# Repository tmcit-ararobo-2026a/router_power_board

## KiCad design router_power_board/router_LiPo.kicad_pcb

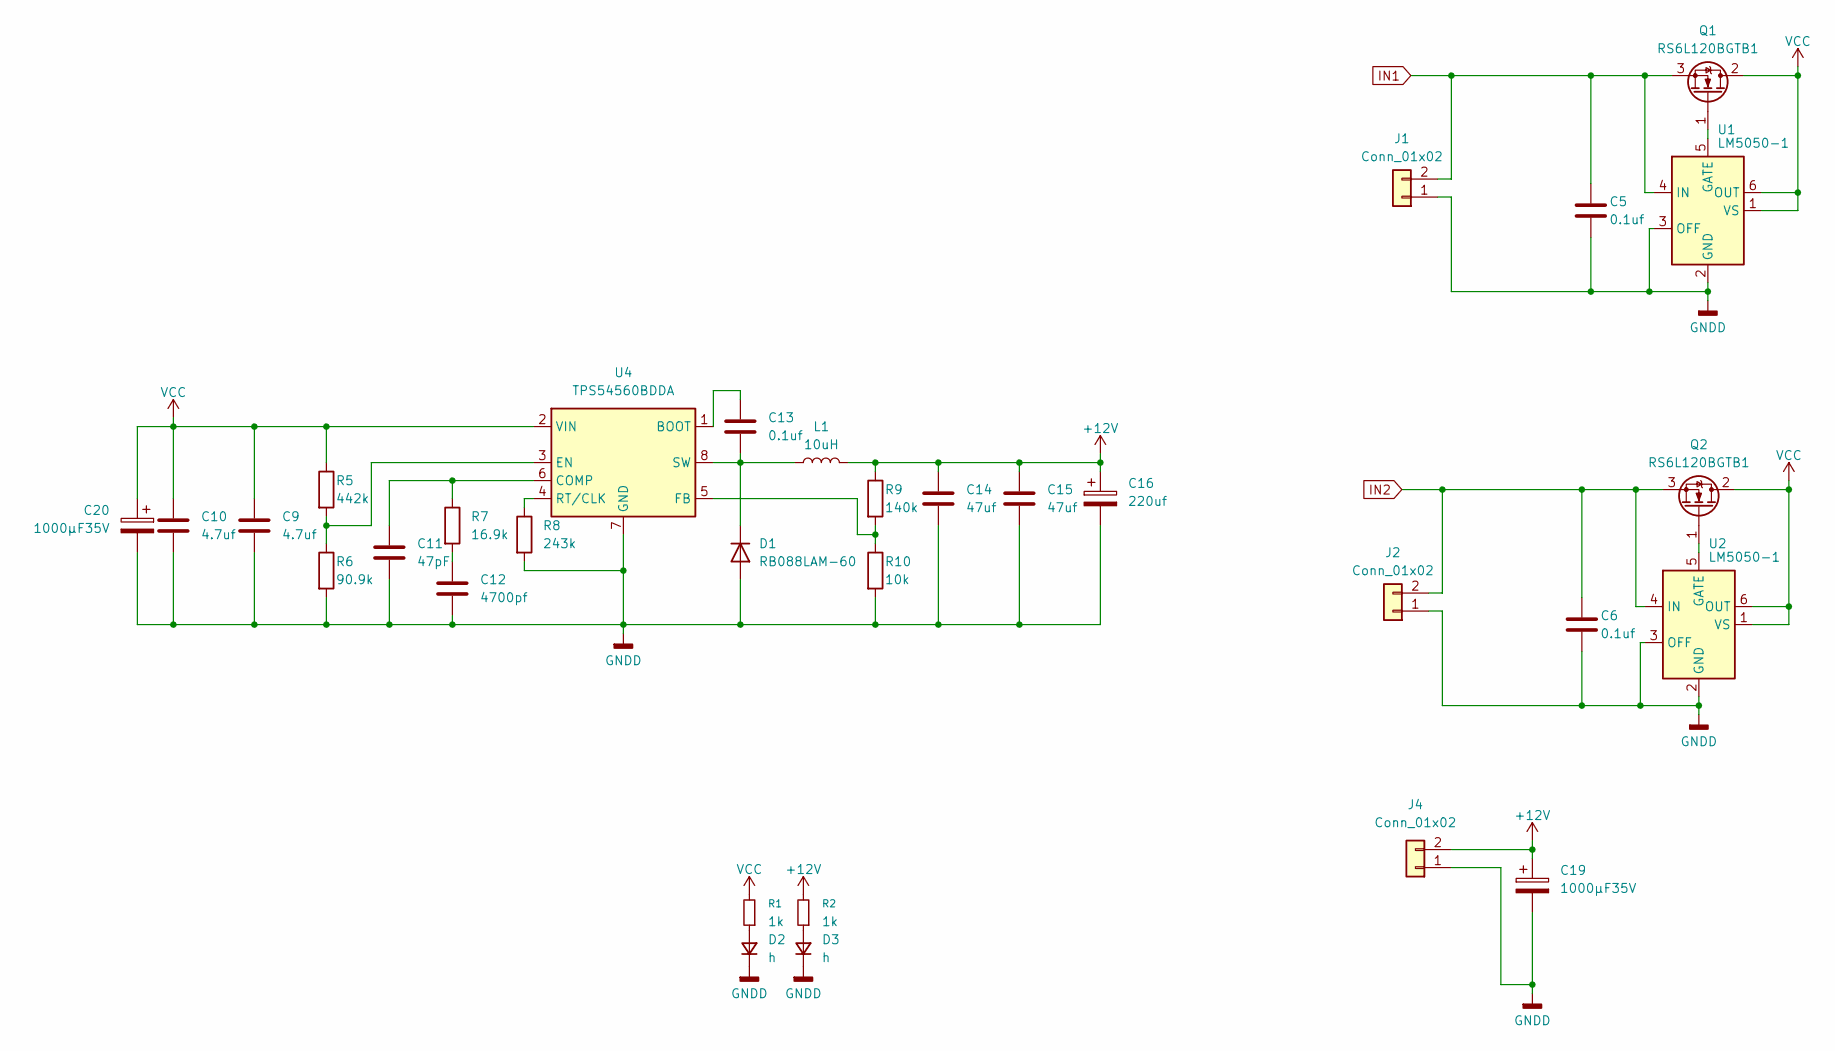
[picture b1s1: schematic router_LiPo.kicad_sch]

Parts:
C5, C6, C13: 0.1uf; C_0603_1608Metric_Pad1.08x0.95mm_HandSolder
C9, C10: 4.7uf; C_1210_3225Metric_Pad1.33x2.70mm_HandSolder
C11: 47pF; C_0603_1608Metric_Pad1.08x0.95mm_HandSolder
C12: 4700pf; C_0603_1608Metric_Pad1.08x0.95mm_HandSolder
C14, C15: 47uf; C_1210_3225Metric_Pad1.33x2.70mm_HandSolder
C16: 220uf; C_Radial_D8.0mm_H7.0mm_P3.50mm
C19, C20: 1000μF35V; CP_Radial_D12.5mm_P5.00mm
D1: RB088LAM-60; D_SOD-128
D2, D3: h; D_0603_1608Metric_Pad1.05x0.95mm_HandSolder
J1, J2: Conn_01x02; AMASS_XT60PW-M_1x02_P7.20mm_Horizontal
J4: Conn_01x02; AMASS_XT60PW-F_1x02_P7.20mm_Horizontal
L1: 10uH; XAL6060103MEC
Q1, Q2: RS6L120BGTB1; SOP_Advance
R1, R2: 1k; R_0603_1608Metric_Pad0.98x0.95mm_HandSolder
R5: 442k; R_0603_1608Metric_Pad0.98x0.95mm_HandSolder
R6: 90.9k; R_0603_1608Metric_Pad0.98x0.95mm_HandSolder
R7: 16.9k; R_0603_1608Metric_Pad0.98x0.95mm_HandSolder
R8: 243k; R_0603_1608Metric_Pad0.98x0.95mm_HandSolder
R9: 140k; R_0603_1608Metric_Pad0.98x0.95mm_HandSolder
R10: 10k; R_0603_1608Metric_Pad0.98x0.95mm_HandSolder
U1, U2: LM5050-1; TSOT-23-6
U4: TPS54560BDDA; Texas_R-PDSO-G8_EP2.95x4.9mm_Mask2.4x3.1mm_ThermalVias

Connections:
+12V: C14.1, C15.1, C16.1, C19.1, J4.2, L1.2, R2.2, R9.1
GNDD: C5.2, C6.2, C9.2, C10.2, C11.2, C12.2, C14.2, C15.2, C16.2, C19.2, C20.2, D1.2 (A), D2.1 (K), D3.1 (K), J1.1, J2.1, J4.1, R6.2, R8.2, R10.2, U1.2 (GND), U1.3 (OFF), U2.2 (GND), U2.3 (OFF), U4.7 (GND), U4.9 (GND)
IN1: C5.1, J1.2, Q1.3 (S), U1.4 (IN)
IN2: C6.1, J2.2, Q2.3 (S), U2.4 (IN)
unnamed: C12.1, R7.2
unnamed: C13.2, D1.1 (K), L1.1, U4.8 (SW)
unnamed: D2.2 (A), R1.1
unnamed: D3.2 (A), R2.1
unnamed: Q1.1 (G), U1.5 (GATE)
unnamed: Q2.1 (G), U2.5 (GATE)
unnamed: C13.1, U4.1 (BOOT)
unnamed: C11.1, R7.1, U4.6 (COMP)
unnamed: R5.2, R6.1, U4.3 (EN)
unnamed: R9.2, R10.1, U4.5 (FB)
unnamed: R8.1, U4.4 (RT/CLK)
VCC: C9.1, C10.1, C20.1, Q1.2 (D), Q2.2 (D), R1.2, R5.1, U1.1 (VS), U1.6 (OUT), U2.1 (VS), U2.6 (OUT), U4.2 (VIN)

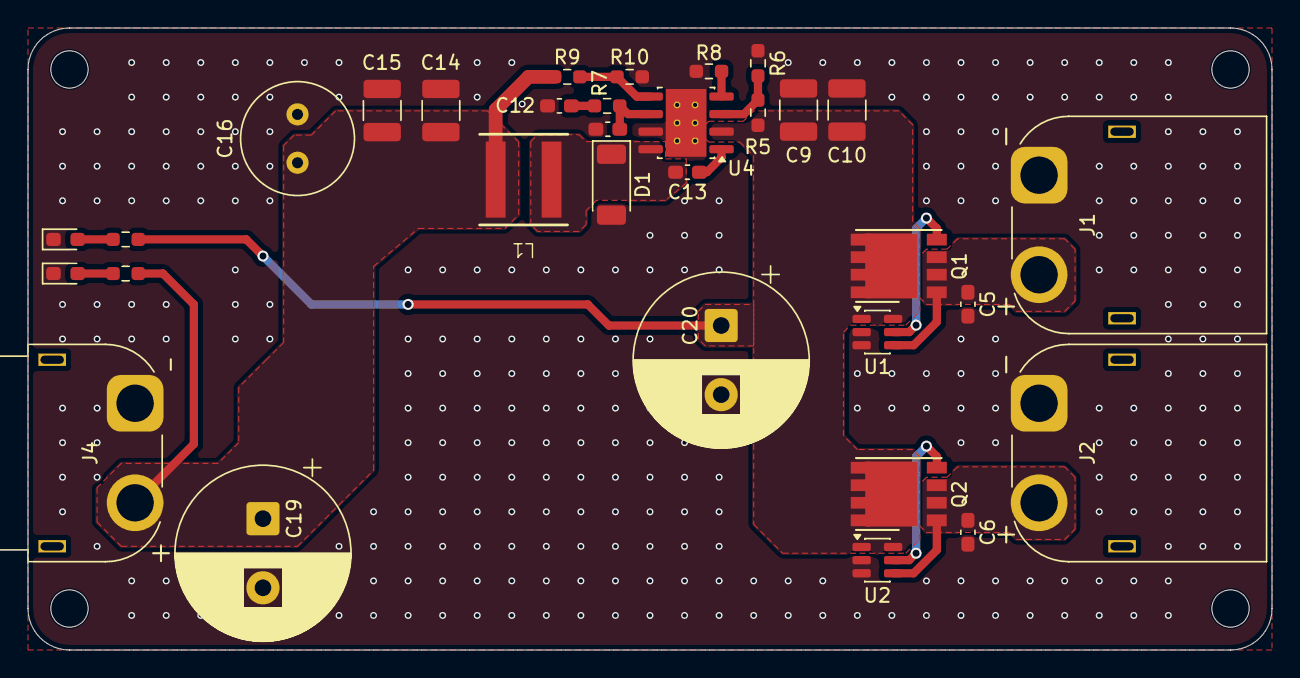
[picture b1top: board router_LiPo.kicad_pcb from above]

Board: 2 copper layers, 90.0 x 45.0 mm, 32 parts (0 on the bottom side), 16 nets.

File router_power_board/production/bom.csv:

Designator,Footprint,Quantity,Value,LCSC Part #
"C10, C9",1210,2,4.7uf,
C11,0603,1,47pF,
C12,0603,1,4700pf,
"C13, C5, C6",0603,3,0.1uf,
"C14, C15",1210,2,47uf,
C16,C_Radial_D8.0mm_H7.0mm_P3.50mm,1,220uf,
"C19, C20",CP_Radial_D12.5mm_P5.00mm,2,1000μF35V,
D1,D_SOD-128,1,RB088LAM-60,
"D2, D3",0603,2,h,
"J1, J2",AMASS_XT60PW-M_1x02_P7.20mm_Horizontal,2,Conn_01x02,
J4,AMASS_XT60PW-F_1x02_P7.20mm_Horizontal,1,Conn_01x02,
L1,XAL6060103MEC,1,10uH,
"Q1, Q2",SOP_Advance,2,RS6L120BGTB1,
"R1, R2",0603,2,1k,
R10,0603,1,10k,
R5,0603,1,442k,
R6,0603,1,90.9k,
R7,0603,1,16.9k,
R8,0603,1,243k,
R9,0603,1,140k,
"U1, U2",TSOT-23-6,2,LM5050-1,
U4,Texas_R-PDSO-G8_EP2.95x4.9mm_Mask2.4x3.1mm_ThermalVias,1,TPS54560BDDA,
